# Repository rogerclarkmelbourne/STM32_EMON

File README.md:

# STM32_EMON

This repository contains the Eagle files for my STM32 energy monitoring and display projects,  based on the Open Energy Monitor project's work

NOTE. THIS IS A WORK IN PROGRESS, PLEASE CHECK MY DESIGNS BEFORE COMMITTING TO GETTING A PCB MADE!

The PowerTransmitter board, had 2 faults on the first batch of PCB's. A track was missing (current sense input to the ADC on the STM32),
I also omitted pullups and pulldowns on the ESP8266.
I think the issue with the current input track has been fixed, but the ESP8266 issue still needs to be checked.
 
The PowerReceiver board seems to work, but I've not tested the ESP8266 connections.

The PowerTransmitter, is equivalent to the EMonTX, in that it monitors mains voltages and current, and transmits this data via RF
My PowerTransmistter also has an ILI9341 display, and uses a Nordic nRF905 for RF transmission. 
It also has an ESP8266 - however there is currently a mistake in the schematic and PCB as its missing a pullup or pull down

PowerReceiver is a simple display unit to remotely display the same information on the PowerTransmitter, but it also contains an ESP8266.

The reason the Power Receiver has an ESP8266, is because for when the PowerTransmitter can't be located where there is Wifi coverage, hence the PowerReceiver acts as a bridge to Wifi in this case.

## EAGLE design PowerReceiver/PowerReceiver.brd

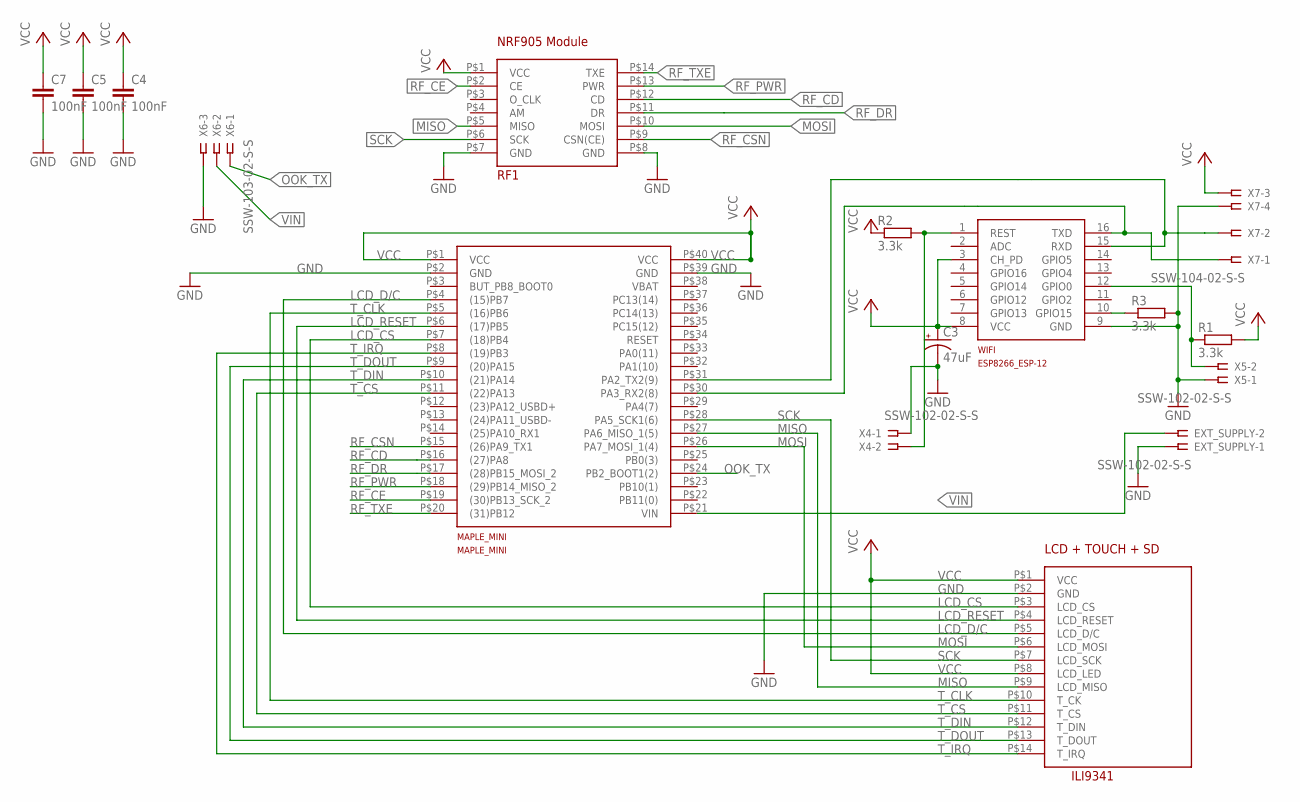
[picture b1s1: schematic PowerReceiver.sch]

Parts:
C3: 47uF; E5-8,5
C4, C5, C7: 100nF; C050-035X075
EXT_SUPPLY: SSW-102-02-S-S
ILI9341: ILI9341_TOUCH_SD; 2.4_INCH
MAPLE_MINI: MAPLE_MINI
R1, R2, R3: 3.3k; 0309V
RF1: NRF905_MODULE; PIN14
WIFI: ESP8266-12; ESP8266-ESP12
X4, X5: SSW-102-02-S-S
X6: SSW-103-02-S-S
X7: SSW-104-02-S-S

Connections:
GND: C3.-, C4.2, C5.2, C7.2, EXT_SUPPLY.1, ILI9341.P$2 (GND), MAPLE_MINI.P$2 (GND), MAPLE_MINI.P$39 (GND), R3.2, RF1.P$7 (GND), RF1.P$8 (GND), WIFI.9 (GND), X4.1, X5.1, X6.3, X7.4
LCD_CS: ILI9341.P$3 (LCD_CS), MAPLE_MINI.P$7 ((18)PB4)
LCD_D/C: ILI9341.P$5 (LCD_D/C), MAPLE_MINI.P$4 ((15)PB7)
LCD_RESET: ILI9341.P$4 (LCD_RESET), MAPLE_MINI.P$6 ((17)PB5)
MISO: ILI9341.P$9 (LCD_MISO), MAPLE_MINI.P$27 (PA6_MISO_1(5)), RF1.P$5 (MISO)
MOSI: ILI9341.P$6 (LCD_MOSI), MAPLE_MINI.P$26 (PA7_MOSI_1(4)), RF1.P$10 (MOSI)
unnamed: R3.1, WIFI.10 (GPIO15)
unnamed: MAPLE_MINI.P$30 (PA3_RX2(8)), WIFI.16 (TXD), X7.1
unnamed: MAPLE_MINI.P$31 (PA2_TX2(9)), WIFI.15 (RXD), X7.2
unnamed: R2.2, WIFI.1 (REST), X4.2
unnamed: R1.1, WIFI.12 (GPIO0), X5.2
OOK_TX: MAPLE_MINI.P$24 (PB2_BOOT1(2)), X6.1
RF_CD: MAPLE_MINI.P$16 ((27)PA8), RF1.P$12 (CD)
RF_CE: MAPLE_MINI.P$19 ((30)PB13_SCK_2), RF1.P$2 (CE)
RF_CSN: MAPLE_MINI.P$15 ((26)PA9_TX1), RF1.P$9 (CSN(CE))
RF_DR: MAPLE_MINI.P$17 ((28)PB15_MOSI_2), RF1.P$11 (DR)
RF_PWR: MAPLE_MINI.P$18 ((29)PB14_MISO_2), RF1.P$13 (PWR)
RF_TXE: MAPLE_MINI.P$20 ((31)PB12), RF1.P$14 (TXE)
SCK: ILI9341.P$7 (LCD_SCK), MAPLE_MINI.P$28 (PA5_SCK1(6)), RF1.P$6 (SCK)
T_CLK: ILI9341.P$10 (T_CK), MAPLE_MINI.P$5 ((16)PB6)
T_CS: ILI9341.P$11 (T_CS), MAPLE_MINI.P$11 ((22)PA13)
T_DIN: ILI9341.P$12 (T_DIN), MAPLE_MINI.P$10 ((21)PA14)
T_DOUT: ILI9341.P$13 (T_DOUT), MAPLE_MINI.P$9 ((20)PA15)
T_IRQ: ILI9341.P$14 (T_IRQ), MAPLE_MINI.P$8 ((19)PB3)
VCC: C3.+, C4.1, C5.1, C7.1, ILI9341.P$1 (VCC), ILI9341.P$8 (LCD_LED), MAPLE_MINI.P$1 (VCC), MAPLE_MINI.P$40 (VCC), R1.2, R2.1, RF1.P$1 (VCC), WIFI.3 (CH_PD), WIFI.8 (VCC), X7.3
VIN: EXT_SUPPLY.2, MAPLE_MINI.P$21 (VIN), X6.2

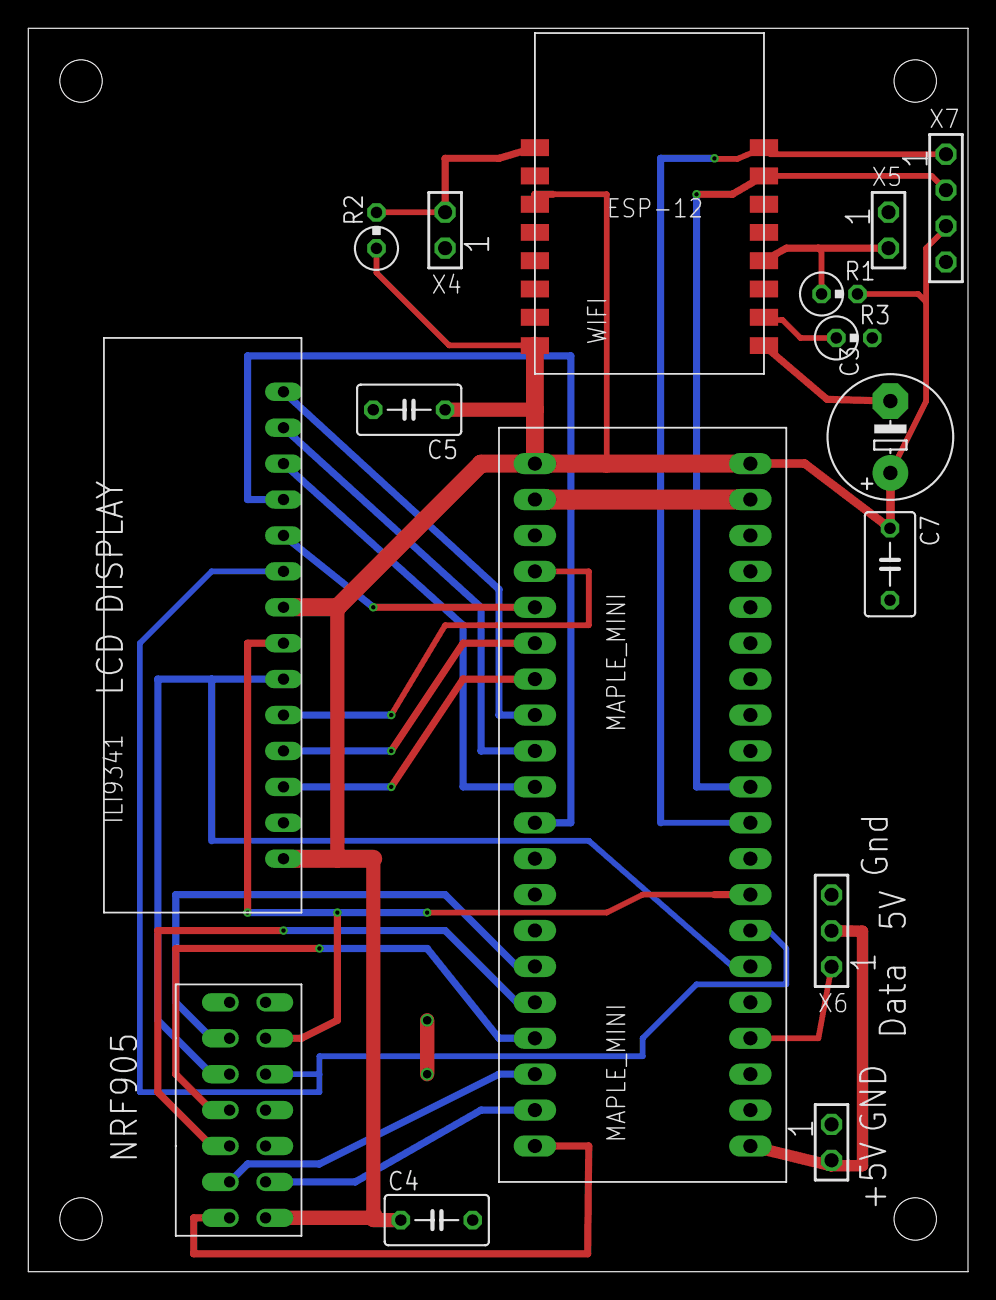
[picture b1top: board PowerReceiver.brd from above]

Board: 2 copper layers, 66.5 x 87.9 mm, 16 parts (0 on the bottom side), 26 nets.
